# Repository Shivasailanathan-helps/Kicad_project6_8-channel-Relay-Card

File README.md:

# Kicad_project6_8-channel-Relay-Card
Modular 8-channel power relay PCB designed for high-current AC/DC switching. Driven by a ULN2803A Darlington IC for 5V TTL/CMOS logic compatibility, it features THT relays, flyback diode protection, individual LED status indicators, DIP switch control, side screw terminals, and 4 aligned M3 mounting holes.

This is a professional 8-channel power relay interface board designed in KiCad for industrial automation and microcontroller load switching applications. Powered by an onboard ULN2803A Darlington transistor array IC, the module translates 5V TTL/CMOS logic signals into high-current switching for up to 8 independent AC/DC electrical loads. The 2-layer PCB features an ergonomic dual-column mechanical architecture, outward-facing Phoenix screw terminal breakouts, flyback diode inductive protection, channel status LEDs, a master power slide switch, 4 aligned M3 mounting holes, and a continuous bottom-layer ground plane.

### Features:
1) Microcontroller & Driver Architecture: ULN2803A Darlington Transistor Array (DIP-18) featuring 2.7kΩ internal base resistors, allowing direct 5V logic control from microcontrollers (Arduino, ESP32, STM32, or Raspberry Pi) without external current-limiting base drivers.
2) 8-Channel High-Power Relay Array: 8 x Omron G5LE-1 SPDT Through-Hole (THT) relays (K1–K8) capable of switching high-voltage AC (250V AC/10A) and DC (30V DC/ 10A) circuits.
3) Inductive Flyback & Visual Diagnostics: 8 x SMD flyback protection diodes (D2, D5, D7, D9, D14, D15, D16, D17, 1206) across relay coils to absorb inductive voltage spikes, paired with 8 x channel activation status LEDs (D3, D4, D6, D8, D10, D11, D12, D13, 1206) and 1 x main power LED (D1).
4) Input Signal Conditioning & Power Control: 16 x 10kΩ SMD resistors (R1–R16, 0805) forming a dedicated input pull-down network and series signal-limiting array, integrated with a 1-position SPST DIP slide switch (SW1) for master power isolation.
5) Robust Terminal Breakout Layout: 8 x 3-pin 5.08mm pitch Phoenix Contact screw terminal blocks (J3–J10) breaking out Normally Open (NO), Common (COM), and Normally Closed (NC) load lines toward the outer PCB edges, with a 2-pin 5.08mm Phoenix terminal (J2) for logic supply (VCC/GND) and an 8-pin 2.54mm pin header (J1) for logic inputs.
6) Enclosure-Ready Mechanical Layout: Symmetric dual-row relay column layout with central logic spine, smooth Edge.Cuts corner fillets, and 4 corner-aligned $3.2\text{mm}$ M3 mounting hole pads (H1, H3, H5, H6).

### Process:
Phase 1: Schematic Capture & Footprint Assignment:
1.1) Schematic & Netlist Setup: Captured the 8-channel relay sub-circuits, ULN2803A driver stage, input pull-down network, status LEDs, and power decoupling block (C1 100nF, C2 100µF). Established clear net connections (INPUT1–INPUT8, COM, VCC, GND) and passed Electrical Rules Check (ERC) with 0 errors and 0 warnings.
1.2) IPC-7351 Footprint Assignment: Assigned standardized footprints across all components (Package_DIP:DIP-18_W7.62mm_LongPads for U1, Relay_THT:Relay_SPDT_Omron-G5LE-1 for K1–K8, TerminalBlock_Phoenix_MKDS-1,5 for J2–J10, Resistor_SMD:R_0805_2012Metric, Diode_SMD:D_1206_3216Metric, and LED_SMD:LED_1206_3216Metric).

Phase 2: PCB Layout & Physical RoutingComponent Placement & Symmetry: 
2.1) Transferred schematic data to PCB Editor (F8). Positioned the 8 relays into two symmetrical 4-relay columns along the left and right edges, placing the ULN2803A IC, passive arrays, power switch, and status LEDs inside the central channel to minimize ratsnest clutter.
2.2) Edge Geometry & Alignment: Created the board perimeter on Edge.Cuts with 5mm corner radius fillets. Aligned the 4 corner mounting holes (H1, H3, H5, H6) to identical X/Y coordinate offsets to ensure strain-free mounting in standard enclosures.
2.3) Trace Routing & Zone Fills: Routed low-voltage signal paths, widened power and AC relay contacts, poured a continuous Bottom Copper (B.Cu) GND plane, and validated all clearances with Design Rules Check (DRC).

### Extras:
1) Why Use a ULN2803A Darlington Array for Relay Driving?

Microcontroller I/O pins typically source/sink a maximum of 10mA–20mA, whereas standard 5V electromechanical relay coils require 70mA–90mA each to energize. Activating all 8 relays simultaneously demands over 600mA—far exceeding direct MCU output capabilities. The ULN2803A integrates 8 NPN Darlington pairs capable of sinking up to 500mA per channel with internal 2.7k ohm series base resistors, allowing safe, direct control straight from logic lines without external base driving circuitry.

2) Why the ULN2803A (3rd Series) Variant Was Selected:

The ULN2800 family consists of five distinct input-stage variants (ULN2801A through ULN2805A), each tailored for specific input logic family voltage levels and gate structures:
2.1) ULN2801A: General-purpose Darlington array without internal base resistors. Using this variant would require adding 8 external base resistors on the PCB to limit microcontroller pin current.
2.2) ULN2802A: Designed specifically for 14V–25V PMOS logic; a standard 5V logic signal cannot provide enough voltage to drive this input stage.
2.3) ULN2803A (Selected): Features an internal 2.7k ohm series resistor per channel, specifically optimized for 5V TTL and 5V CMOS logic (such as ATmega328P, Arduino, 5V PICs, and standard logic gates). It draws roughly 1.35mA per input pin at 5V, perfectly saturating the Darlington pair while keeping MCU current minimal.
2.4) ULN2804A: Features a higher 10.5k ohm internal series resistor intended for 6V–15V CMOS logic. Driving this variant with 5V logic fails to supply enough base current to fully saturate the transistors under heavy relay coil loads.
2.5) ULN2805A: Designed for higher-voltage 6V–15V PMOS/CMOS logic applications.

3) Why Are Flyback Diodes (D2, D5, D7, D9, D14–D17) Required Across Relay Coils?
   
Relay coils are inductors (L). When a Darlington channel turns off to deactivate a relay, the sudden collapse of the coil's magnetic field creates a high-voltage reverse voltage spike (V = -L*di/dt) known as inductive kickback. The parallel flyback diodes provide a safe recirculation path for this energy, protecting the ULN2803A transistors from high-voltage breakdown.

### Problems Faced:

Zone Fill Out-of-Date Warnings during Gerber Generation:
Problem: KiCad issued a Zone fills are out-of-date. Refill? prompt during Gerber plot generation.
Theory: Component repositioning and trace modifications performed after initial copper zone creation alter pad clearance boundaries, leaving the ground plane out of sync.
Rectification: Executed a full copper zone recalculation (B) prior to plotting, ensuring all Gerber layers (F_Cu, B_Cu, F_Mask, B_Mask, Edge_Cuts, PTH/NPTH) reflected accurate clearance gaps and copper pours.

### Outputs:

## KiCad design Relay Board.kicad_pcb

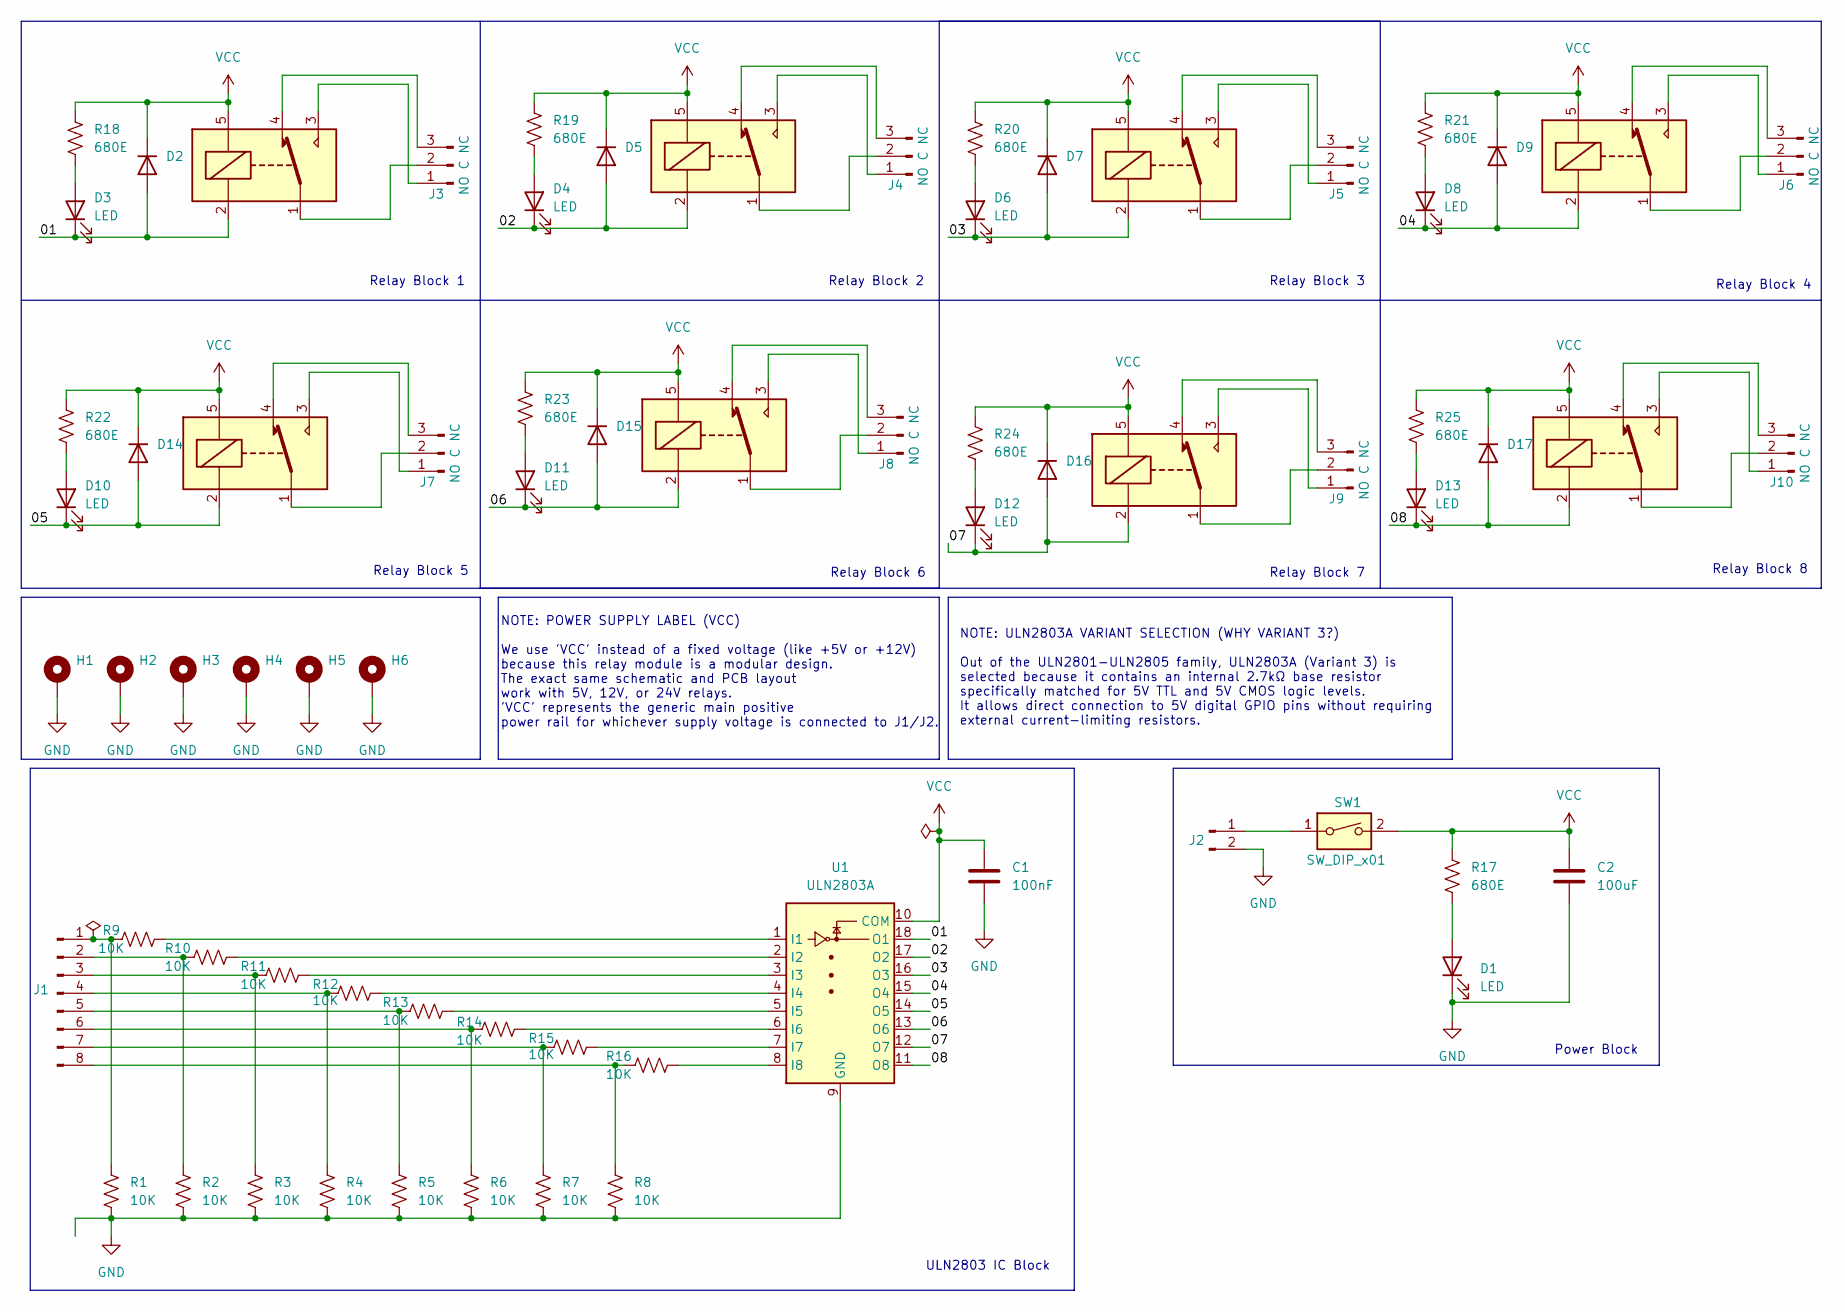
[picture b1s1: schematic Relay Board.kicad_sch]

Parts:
C1: 100nF; C_0805_2012Metric
C2: 100uF; C_0805_2012Metric
D1, D3, D4, D6, D8, D10, D11, D12, D13: LED; LED_1206_3216Metric
D2, D5, D7, D9, D14, D15, D16, D17: D; D_1206_3216Metric
H1, H2, H3, H4, H5, H6: MountingHole_Pad; MountingHole_2.5mm_Pad_Via
J1: Conn_01x08_Pin; PinHeader_1x08_P2.54mm_Vertical
J2: Conn_01x02_Pin; TerminalBlock_Phoenix_MKDS-1,5-2-5.08_1x02_P5.08mm_Horizont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
J3, J4, J5, J6, J7, J8, J9, J10: NO C NC; TerminalBlock_Phoenix_MKDS-1,5-3-5.08_1x03_P5.08mm_Horizont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
K1, K2, K3, K4, K5, K6, K7, K8: G5LE-1; Relay_SPDT_Omron-G5LE-1
R1, R2, R3, R4, R5, R6, R7, R8, R9, R10, R11, R12, R13, R14, R15, R16: 10K; R_0805_2012Metric
R17, R18, R19, R20, R21, R22, R23, R24, R25: 680E; R_0805_2012Metric
SW1: SW_DIP_x01; SW_DIP_SPSTx01_Slide_9.78x4.72mm_W7.62mm_P2.54mm
U1: ULN2803A; DIP-18_W7.62mm_LongPads

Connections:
/01: D2.2 (A), D3.1 (K), K1.2, U1.18 (O1)
/02: D4.1 (K), D5.2 (A), K2.2, U1.17 (O2)
/03: D6.1 (K), D7.2 (A), K3.2, U1.16 (O3)
/04: D8.1 (K), D9.2 (A), K4.2, U1.15 (O4)
/05: D10.1 (K), D14.2 (A), K5.2, U1.14 (O5)
/06: D11.1 (K), D15.2 (A), K6.2, U1.13 (O6)
/07: D12.1 (K), D16.2 (A), K7.2, U1.12 (O7)
/08: D13.1 (K), D17.2 (A), K8.2, U1.11 (O8)
GND: C1.2, C2.2, D1.1 (K), H1.1 (1_1), H2.1 (1_1), H3.1 (1_1), H4.1 (1_1), H5.1 (1_1), H6.1 (1_1), J2.2, R1.2, R2.2, R3.2, R4.2, R5.2, R6.2, R7.2, R8.2, U1.9 (GND)
unnamed: D1.2 (A), R17.2
unnamed: D3.2 (A), R18.2
unnamed: D4.2 (A), R19.2
unnamed: D6.2 (A), R20.2
unnamed: D8.2 (A), R21.2
unnamed: D10.2 (A), R22.2
unnamed: D11.2 (A), R23.2
unnamed: D12.2 (A), R24.2
unnamed: D13.2 (A), R25.2
unnamed: J1.1, R1.1, R9.1
unnamed: J1.2, R2.1, R10.1
unnamed: J1.3, R3.1, R11.1
unnamed: J1.4, R4.1, R12.1
unnamed: J1.5, R5.1, R13.1
unnamed: J1.6, R6.1, R14.1
unnamed: J1.7, R7.1, R15.1
unnamed: J1.8, R8.1, R16.1
unnamed: J2.1, SW1.1
unnamed: J3.1, K1.3
unnamed: J3.2, K1.1
unnamed: J3.3, K1.4
unnamed: J4.1, K2.3
unnamed: J4.2, K2.1
unnamed: J4.3, K2.4
unnamed: J5.1, K3.3
unnamed: J5.2, K3.1
unnamed: J5.3, K3.4
unnamed: J6.1, K4.3
unnamed: J6.2, K4.1
unnamed: J6.3, K4.4
unnamed: J7.1, K5.3
unnamed: J7.2, K5.1
unnamed: J7.3, K5.4
unnamed: J8.1, K6.3
unnamed: J8.2, K6.1
unnamed: J8.3, K6.4
unnamed: J9.1, K7.3
unnamed: J9.2, K7.1
unnamed: J9.3, K7.4
unnamed: J10.1, K8.3
unnamed: J10.2, K8.1
unnamed: J10.3, K8.4
unnamed: R9.2, U1.1 (I1)
unnamed: R10.2, U1.2 (I2)
unnamed: R11.2, U1.3 (I3)
unnamed: R12.2, U1.4 (I4)
unnamed: R13.2, U1.5 (I5)
unnamed: R14.2, U1.6 (I6)
unnamed: R15.2, U1.7 (I7)
unnamed: R16.2, U1.8 (I8)
VCC: C1.1, C2.1, D2.1 (K), D5.1 (K), D7.1 (K), D9.1 (K), D14.1 (K), D15.1 (K), D16.1 (K), D17.1 (K), K1.5, K2.5, K3.5, K4.5, K5.5, K6.5, K7.5, K8.5, R17.1, R18.1, R19.1, R20.1, R21.1, R22.1, R23.1, R24.1, R25.1, SW1.2, U1.10 (COM)

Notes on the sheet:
Relay Block 3
NOTE: POWER SUPPLY LABEL (VCC) We use 'VCC' instead of a fixed voltage (like +5V or +12V) because this relay module is a modular design. The exact same schematic and PCB layout work with 5V, 12V, or 24V relays. 'VCC' represents the generic main positive power rail for whichever supply voltage is co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
Relay Block 8
Power Block
ULN2803 IC Block
Relay Block 2
Relay Block 6
Relay Block 5
Relay Block 7
Relay Block 4
NOTE: ULN2803A VARIANT SELECTION (WHY VARIANT 3?) Out of the ULN2801-ULN2805 family, ULN2803A (Variant 3) is selected because it contains an internal 2.7kΩ base resistor specifically matched for 5V TTL and 5V CMOS logic levels. It allows direct connection to 5V digital GPIO pins without requiring e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
Relay Block 1

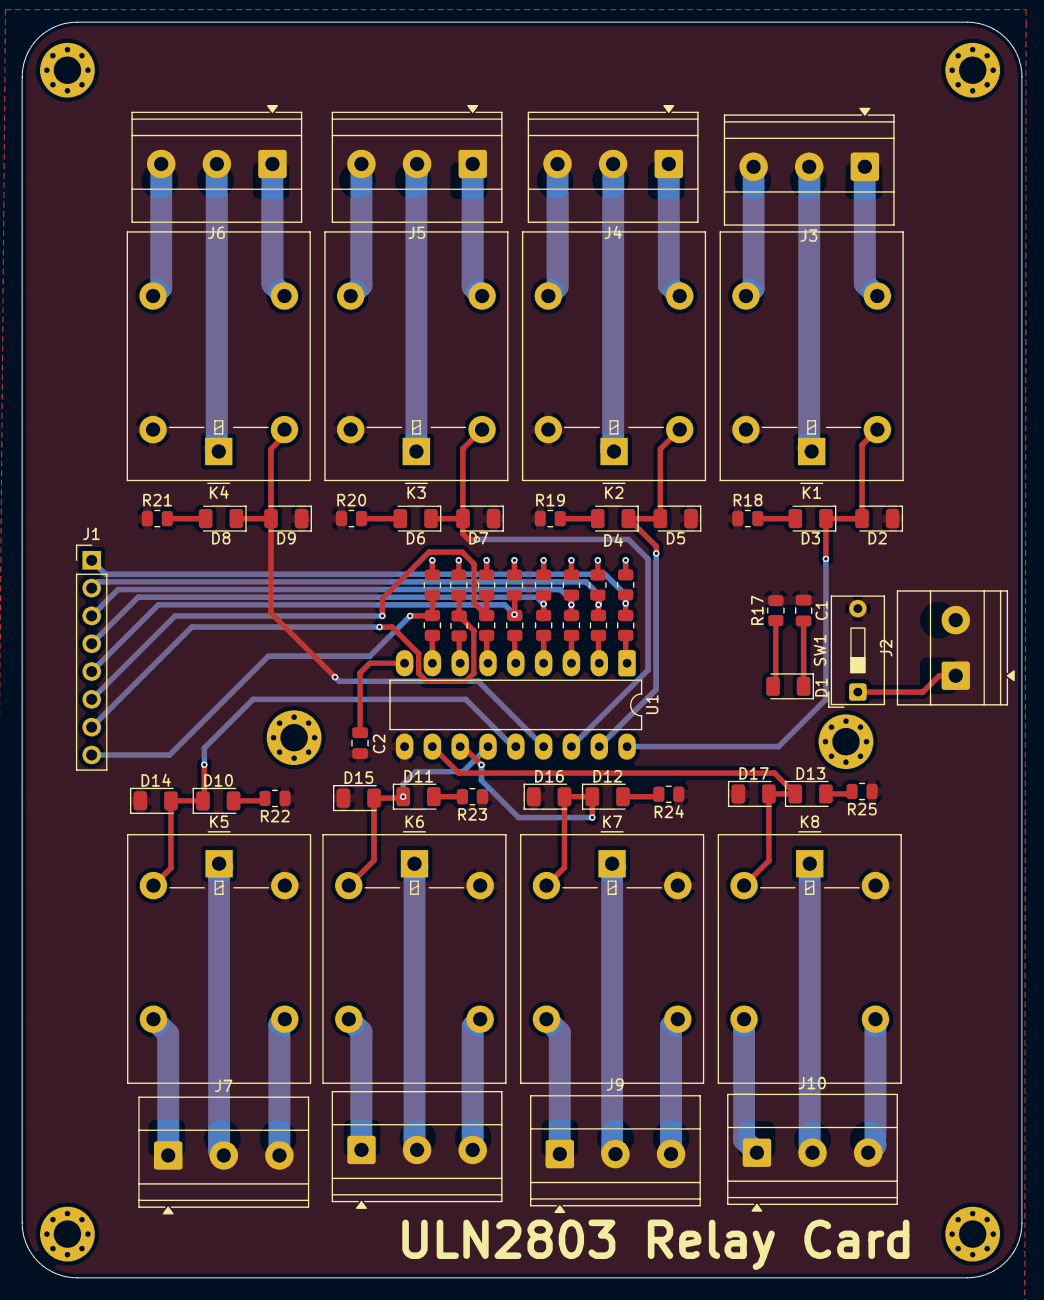
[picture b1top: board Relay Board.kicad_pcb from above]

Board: 2 copper layers, 91.3 x 114.7 mm, 70 parts (0 on the bottom side), 60 nets.
